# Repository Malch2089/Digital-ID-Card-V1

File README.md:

# Digital ID Card V1

Imagine 10 years from now you got lucky and a trillionaire gave you his business card it won't be an ordinary one, it's as thick as a debit-card with an e-ink display featuring all his details. But since this project costed me around $45 to make so don't expect any business man could afford it, it's just a cool concept.

I also planned one more use but that will not work if this is launched as a product. The other use is feeding all your id cards like adhar, pan, voter in one single card.  

## Hardware Overview

The PCB is built around:

- **ESP32-C3-MINI-1** as the main microcontroller (Wi-Fi/BLE enabled, for future wireless updates)
- **MCP73831** LiPo battery charge controller, fed via **USB-C**
- **AP2112K-3.3** linear regulator to supply a clean 3.3V rail
- An 8-pin header for an **E-ink display module** (generic SPI e-paper panel)
- **Boot** and **Reset** push buttons for the ESP32-C3
- Supporting passives (decoupling capacitors, pull-up/pull-down resistors)

The enclosure is a 3D-printed case (see `Case design/`) sized to hold the PCB and battery like a standard ID card/badge.

## Repository Structure

```
Digital-ID-Card-V1/
├── Case design/     # 3D-printed enclosure design files
├── Firmware/         # ESP32-C3 firmware (C++)
├── PCB/             # KiCad schematic, PCB layout, and project files
└── README.md
```

## Bill of Materials (BOM)

This BOM reflects the components placed on the current PCB revision, extracted directly from the KiCad schematic.

| Ref. Designator(s) | Component | Value / Part Number | Footprint / Package | Qty | Function | Links |
|---|---|---|---|---|---|---|
| U3 | Microcontroller | ESP32-C3-MINI-1 (Espressif) | ESP32-C3-MINI-1 module | 1 | Main processor, Wi-Fi/BLE, drives the E-ink display | https://documentation.espressif.com/esp32-c3-mini-1_datasheet_en.html |
| U2 | Battery charge controller | MCP73831T-2-OT | SOT-23-5 | 1 | Charges the LiPo battery from USB-C | https://www.onlinecomponents.com/en/productdetail/microchip-technology/mcp73831t2aciot-44791170.html?utm_campaign=searchads360feed&utm_content=instock&utm_term=MCP73831T-2ACI2FOT&&msclkid=59ce51ac125613cdf9c33bd5dda60918&utm_source=bing&utm_medium=cpc&utm_campaign=Tier1_Bing_INTL_Integrated%20Circuits%20-%20ICs&utm_term=battery%20management%20mcp73831t-2aci%2Fot&utm_content=44791170&gclid=59ce51ac125613cdf9c33bd5dda60918&gclsrc=3p.ds&gad_source=7&gad_campaignid=23857443108 |
| U1 | Voltage regulator | AP2112K-3.3 | SOT-23-5 | 1 | Regulates supply down to 3.3V for the ESP32-C3 | https://www.alldatasheet.com/datasheet-pdf/pdf/1354656/DIODES/AP2112K-3.3TRG1.html |
| J2 | USB connector | USB-C receptacle (USB 2.0, 14-pin) | USB-C SMD receptacle | 1 | Power input / charging / programming | https://www.digikey.com/en/product-highlight/c/cui/usb-type-c-connector |
| J1 | Battery connector | 2-pin JST/header (LiPo battery) | 2.54mm pin header, 1x02 | 1 | Connects to LiPo battery pack | https://www.digikey.in/en/products/filter/headers-male-pins/314?utm_source=chatgpt.com |
| E-ink_display1 | Display connector | 8-pin header (generic SPI e-paper) | 2.54mm pin header, 1x08 | 1 | Connects to E-ink display module | https://www.digikey.in/en/products/detail/molex/0010977086/3068123? |
| boot1, reset1 | Push buttons | SW_Push | SMD tactile switch (SW_SPST_TL3342) | 2 | Boot mode select and reset for ESP32-C3 | https://www.digikey.com/en/products/base-product/e-switch/141/TL3342/472571 |
| R1, R2 | Resistor | 5.1 kΩ | 0805 SMD | 2 | USB-C CC line pull-downs (configures as device) | https://www.digikey.com/en/products/detail/yageo/RC0805DR-075K1L/5918898 |
| R3, R4, R5 | Resistor | 10 kΩ | 0805 SMD | 3 | Pull-up/pull-down resistors (boot/reset/strapping) | https://www.digikey.in/en/products/filter/chip-resistor-surface-mount/0805/52 |
| C1, C2, C3 | Capacitor | 10 µF | 0805 SMD | 3 | Power supply decoupling/filtering | https://www.digikey.in/en/products/filter/ceramic-capacitors/62?utm_source=chatgpt.com |

**Not on the PCB BOM (purchased/printed separately):**

| Item | Notes | Links |
|---|---|---|
| LiPo battery | Connects via J1; capacity depends on case size | https://www.adafruit.com/category/574?utm_source=chatgpt.com |
| E-ink display module | Generic SPI e-paper panel, connects via 8-pin header | https://www.waveshare.com/product/displays/e-paper/2.13inch-e-paper.htm?utm_source=chatgpt.com |
| 3D-printed case | See `Case design/` folder for the enclosure files |

## Status

This is a working prototype (V1). Planned improvements include confirming the exact E-ink display model in this BOM and expanding the firmware to support storing/switching between multiple ID profiles.

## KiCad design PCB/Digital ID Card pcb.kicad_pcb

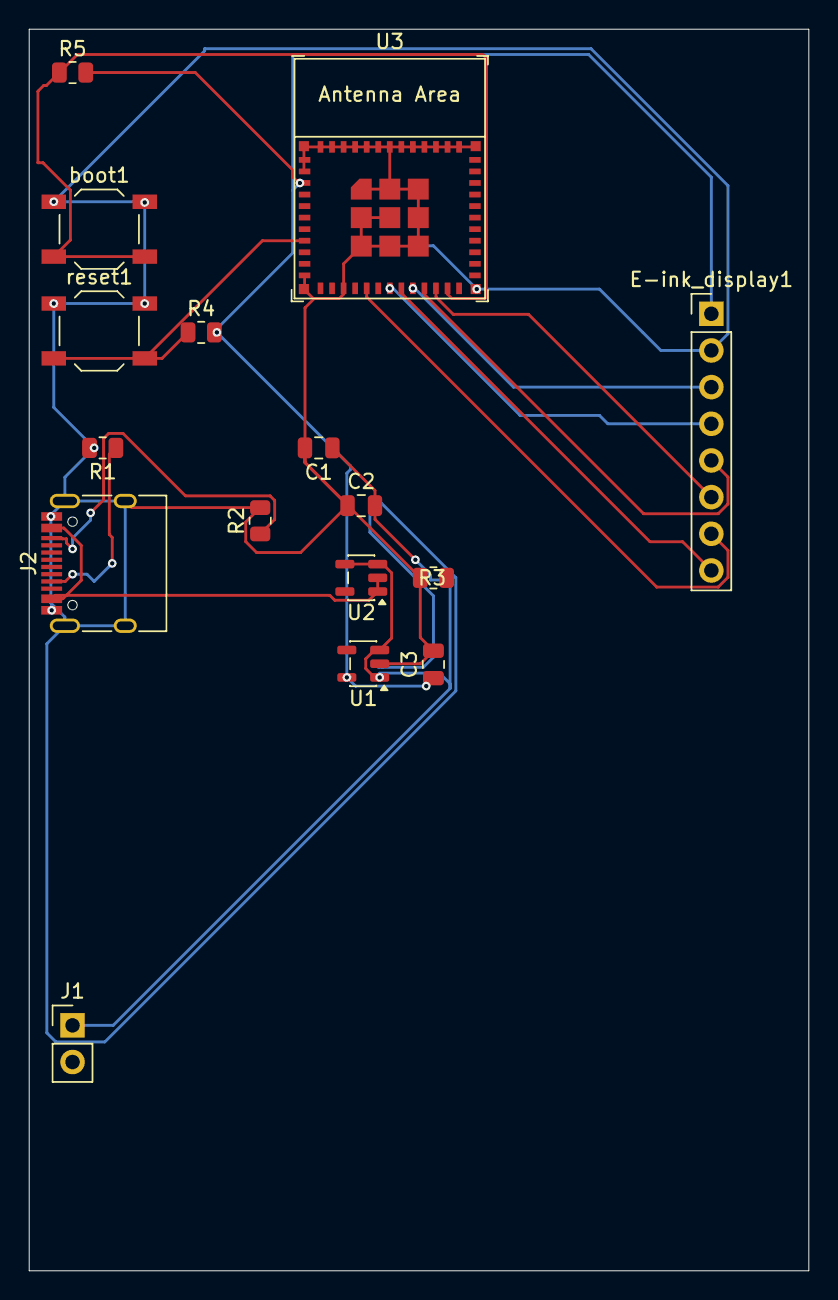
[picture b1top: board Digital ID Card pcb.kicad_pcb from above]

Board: 2 copper layers, 54.0 x 86.0 mm, 16 parts (0 on the bottom side), 14 nets.

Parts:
C1, C2, C3: 10 micro; C_0805_2012Metric
E-ink_display1: Conn_01x08; PinHeader_1x08_P2.54mm_Vertical
J1: LiPo_Battery; PinHeader_1x02_P2.54mm_Vertical
J2: USB_C_Receptacle_USB2.0_14P; USB_C_Receptacle_HRO_TYPE-C-31-M-12
R1, R2: 5.1k; R_0805_2012Metric
R3, R4, R5: 10k; R_0805_2012Metric
U1: AP2112K-3.3; SOT-23-5
U2: MCP73831-2-MC; SOT-23-5
U3: ESP32-C3-MINI-1
boot1: SW_Push; SW_SPST_TL3342
reset1: SW_Push; SW_SPST_TL3342

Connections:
+3V3: C3.1, E-ink_display1.1, R4.2, R5.2, U1.5 (VOUT), U3.3 (3V3)
GND: C1.2, C2.1, C3.2, E-ink_display1.2, J1.2, J2.A1 (GND), J2.A12 (GND), J2.B1 (GND), J2.B12 (GND), J2.S1 (SHIELD), R1.2, R2.2, R3.2, U1.2 (GND), U3.1 (GND), U3.2 (GND), U3.11 (GND), U3.14 (GND), U3.36 (GND), U3.37 (GND), U3.38 (GND), U3.39 (GND), U3.40 (GND), U3.41 (GND), U3.42 (GND), U3.43 (GND), U3.44 (GND), U3.45 (GND), U3.46 (GND), U3.47 (GND), U3.48 (GND), U3.49 (GND), U3.50 (GND), U3.51 (GND), U3.52 (GND), U3.53 (GND), boot1.1, reset1.1
unnamed: E-ink_display1.3, U3.20 (GPIO6)
unnamed: E-ink_display1.4, U3.18 (GPIO4/ADC1_CH4)
unnamed: E-ink_display1.5, U3.21 (GPIO7)
unnamed: E-ink_display1.6, U3.22 (GPIO8)
unnamed: E-ink_display1.7, U3.16 (GPIO10)
unnamed: E-ink_display1.8, U3.19 (GPIO5/ADC2_CH0)
unnamed: C1.1, C2.2, J1.1, U1.1 (VIN), U1.3 (EN), U2.3 (V_{BAT}), U2.4 (V_{BAT})
unnamed: J2.A5 (CC1), R1.1
unnamed: J2.B5 (CC2), R2.1
unnamed: J2.A4 (VBUS), J2.A9 (VBUS), J2.B4 (VBUS), J2.B9 (VBUS), U2.1 (V_{DD}), U2.2 (V_{DD})
unnamed: R4.1, U3.8 (EN/CHIP_PU), reset1.2
unnamed: R5.1, U3.23 (GPIO9), boot1.2

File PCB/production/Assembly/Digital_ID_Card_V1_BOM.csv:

"Designators","Value","Footprint","Quantity","DNP"
"boot1,reset1","SW_Push","Button_Switch_SMD:SW_SPST_TL3342","2",""
"C1-C3","10 micro","Capacitor_SMD:C_0805_2012Metric","3",""
"E-ink_display1","Conn_01x08","Connector_PinHeader_2.54mm:PinHeader_1x08_P2.54mm_Vertical","1",""
"J1","LiPo_Battery","Connector_PinHeader_2.54mm:PinHeader_1x02_P2.54mm_Vertical","1",""
"J2","USB_C_Receptacle_USB2.0_14P","Connector_USB:USB_C_Receptacle_HRO_TYPE-C-31-M-12","1",""
"R1,R2","5.1k","Resistor_SMD:R_0805_2012Metric","2",""
"R3-R5","10k","Resistor_SMD:R_0805_2012Metric","3",""
"U1","AP2112K-3.3","Package_TO_SOT_SMD:SOT-23-5","1",""
"U2","MCP73831-2-OT","Package_TO_SOT_SMD:SOT-23-5","1",""
"U3","ESP32-C3-MINI-1","Espressif:ESP32-C3-MINI-1","1",""

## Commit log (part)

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2026-06-15 files added
2026-06-15 Add images to README
    Add images to README for better visual representation
2026-06-29 Enhance README with project details and structure
    Added detailed project description, hardware overview, BOM, and repository structure.
